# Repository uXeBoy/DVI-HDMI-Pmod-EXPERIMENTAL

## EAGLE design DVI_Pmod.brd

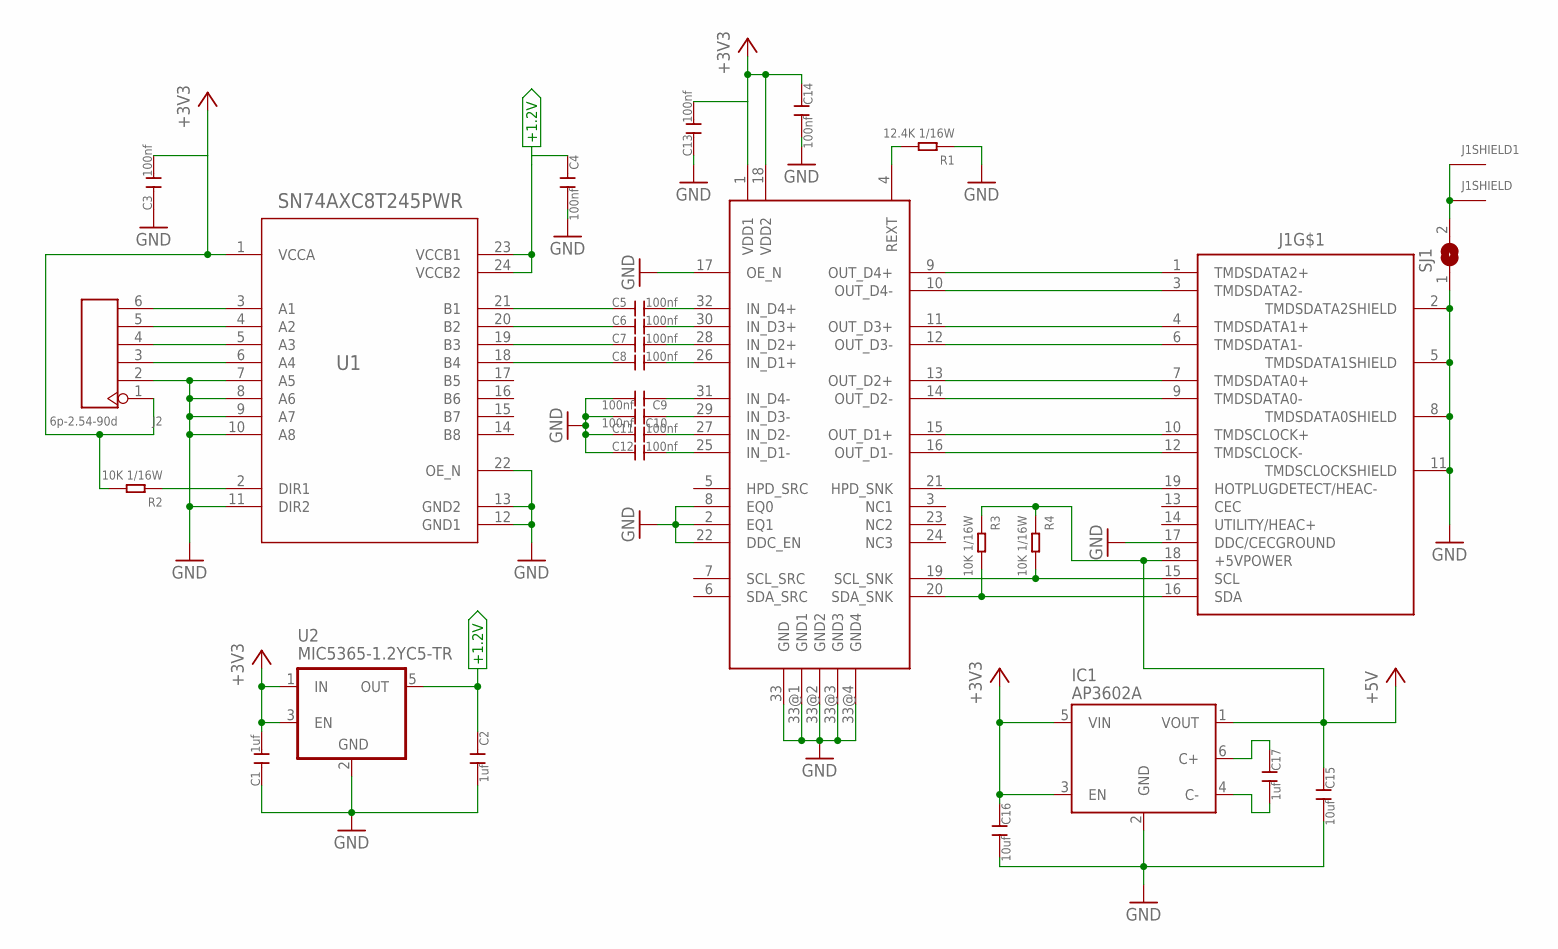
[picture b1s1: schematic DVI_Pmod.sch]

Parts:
C1, C2: 1uf; C0402
C3, C4, C5, C6, C7, C8, C9, C10, C11, C12, C13, C14: 100nf; C0402
C15: 10uf; C0805
C16: 10uf; C0603
C17: 1uf; C0603
IC1: AP3602A; SOT23-6
J1: 685119134923
J2: 6p-2.54-90d; H6-2.54-90D-MALE
R1: 12.4K 1/16W; R0402
R2, R3, R4: 10K 1/16W; R0402
SJ1: SJ
U1: SN74AXC8T245PWR; SOP65P640X120-24N
U2: MIC5365-1.2YC5-TR; SC70-5
U$1: PTN3366; SOT617-3

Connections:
+1.2V: C2.1, C4.1, U1.23 (VCCB1), U1.24 (VCCB2), U2.5 (OUT)
+3V3: C1.2, C3.2, C13.2, C14.1, C16.1, IC1.3 (EN), IC1.5 (VIN), J2.1, R2.2, U1.1 (VCCA), U2.1 (IN), U2.3 (EN), U$1.1 (VDD1), U$1.18 (VDD2)
+5V: C15.1, IC1.1 (VOUT), J1.18 (+5VPOWER), R3.1, R4.1
GND: C1.1, C2.2, C3.1, C4.2, C9.2, C10.2, C11.1, C12.1, C13.1, C14.2, C15.2, C16.2, IC1.2 (GND), J1.2 (TMDSDATA2SHIELD), J1.5 (TMDSDATA1SHIELD), J1.8 (TMDSDATA0SHIELD), J1.11 (TMDSCLOCKSHIELD), J1.17 (DDC/CECGROUND), J2.2, R1.1, SJ1.1, U1.7 (A5), U1.8 (A6), U1.9 (A7), U1.10 (A8), U1.11 (DIR2), U1.12 (GND1), U1.13 (GND2), U1.22 (OE_N), U2.2 (GND), U$1.2 (EQ1), U$1.8 (EQ0), U$1.17 (OE_N), U$1.22 (DDC_EN), U$1.33 (GND), U$1.33@1 (GND1), U$1.33@2 (GND2), U$1.33@3 (GND3), U$1.33@4 (GND4)
unnamed: J1.1 (TMDSDATA2+), U$1.9 (OUT_D4+)
unnamed: J1.3 (TMDSDATA2-), U$1.10 (OUT_D4-)
unnamed: J1.4 (TMDSDATA1+), U$1.11 (OUT_D3+)
unnamed: J1.6 (TMDSDATA1-), U$1.12 (OUT_D3-)
unnamed: J1.7 (TMDSDATA0+), U$1.13 (OUT_D2+)
unnamed: J1.9 (TMDSDATA0-), U$1.14 (OUT_D2-)
unnamed: J1.10 (TMDSCLOCK+), U$1.15 (OUT_D1+)
unnamed: J1.12 (TMDSCLOCK-), U$1.16 (OUT_D1-)
unnamed: C5.2, U$1.32 (IN_D4+)
unnamed: C6.2, U$1.30 (IN_D3+)
unnamed: C7.2, U$1.28 (IN_D2+)
unnamed: C8.2, U$1.26 (IN_D1+)
unnamed: C9.1, U$1.31 (IN_D4-)
unnamed: C10.1, U$1.29 (IN_D3-)
unnamed: C11.2, U$1.27 (IN_D2-)
unnamed: C12.2, U$1.25 (IN_D1-)
unnamed: J2.6, U1.3 (A1)
unnamed: C5.1, U1.21 (B1)
unnamed: C6.1, U1.20 (B2)
unnamed: C7.1, U1.19 (B3)
unnamed: C8.1, U1.18 (B4)
unnamed: J2.5, U1.4 (A2)
unnamed: J2.4, U1.5 (A3)
unnamed: J2.3, U1.6 (A4)
unnamed: R2.1, U1.2 (DIR1)
unnamed: R1.2, U$1.4 (REXT)
unnamed: J1.SHELL (SHIELD), J1.SHELL1 (SHIELD), SJ1.2
unnamed: J1.16 (SDA), R3.2, U$1.20 (SDA_SNK)
unnamed: C17.1, IC1.6 (C+)
unnamed: J1.19 (HOTPLUGDETECT/HEAC-), U$1.21 (HPD_SNK)
unnamed: C17.2, IC1.4 (C-)
unnamed: J1.15 (SCL), R4.2, U$1.19 (SCL_SNK)

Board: 2 copper layers, 28 parts (0 on the bottom side), 36 nets, no tracks yet.

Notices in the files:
parts and their libraries:
InputOutputIO: Copyright: Würth Elektronik
micrel: Copyright (C) 2008, Bob Starr
